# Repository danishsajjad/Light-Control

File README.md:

# Light-Control
 MEL 1 project.

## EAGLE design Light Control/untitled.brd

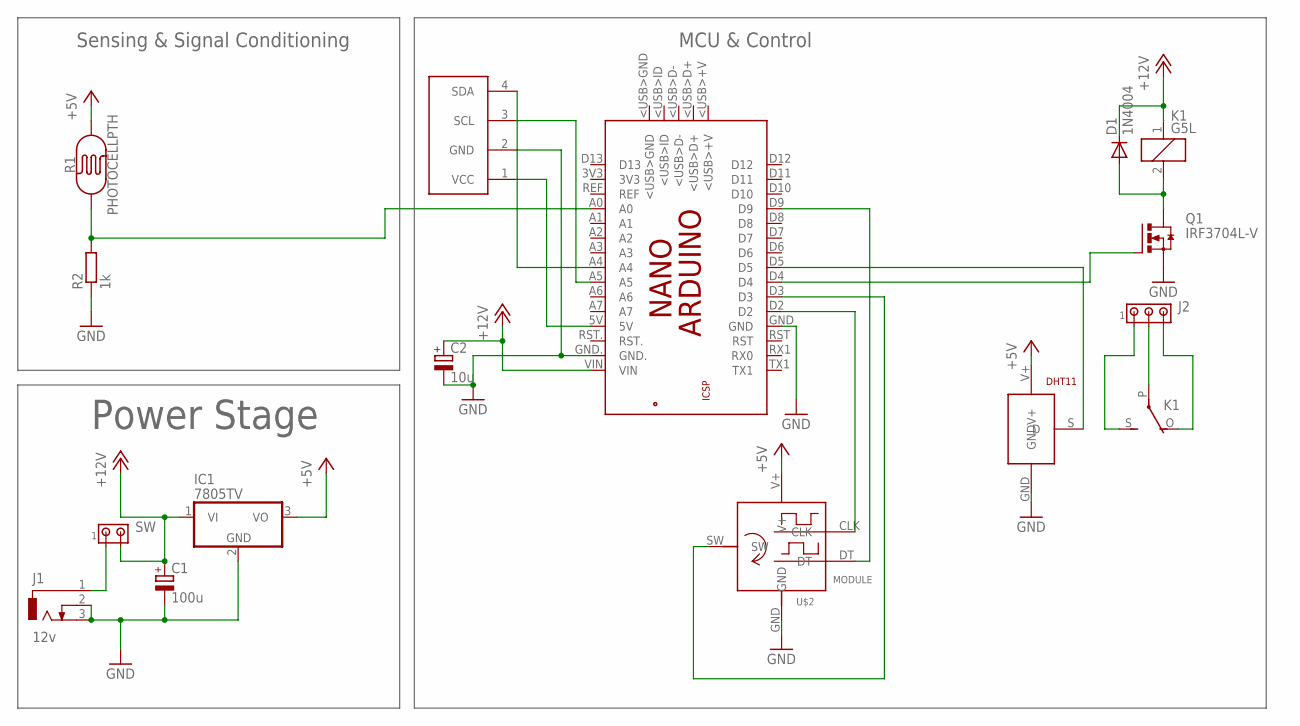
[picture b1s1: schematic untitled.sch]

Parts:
C1: 100u; E3,5-8
C2: 10u; E3,5-8
D1: 1N4004; DO41-10
DHT11: DHT11
IC1: 7805TV; TO220V
J1: 12v; DCJ0303
J2: MTA03-156; 1X3MTA
K1: G5L; G5LE
PCB1: ARDUINO_NANO
Q1: IRF3704L-V; TO262-V
R1: PHOTOCELLPTH; PHOTOCELL
R2: 1k; 0207/7
SW: MTA02-156; 1X2MTA
U$1: I2C_OLED; I2C_OLED_PACKAGE
U$2: MODULE; MODULE/SHEILD

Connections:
+5V: DHT11.V+, IC1.3 (VO), R1.2, U$2.V+
+12V: C1.+, C2.+, D1.C, IC1.1 (VI), K1.1, PCB1.VIN, SW.2
GND: C1.-, C2.-, DHT11.GND, IC1.2 (GND), J1.2, J1.3, PCB1.GND, PCB1.GND., Q1.3 (S), R2.1, U$1.2 (GND), U$2.GND
unnamed: PCB1.A0, R1.1, R2.2
unnamed: PCB1.A4, U$1.4 (SDA)
unnamed: PCB1.A5, U$1.3 (SCL)
unnamed: J1.1, SW.1
unnamed: PCB1.D2, U$2.CLK
unnamed: J2.1, K1.S
unnamed: PCB1.D9, U$2.DT
unnamed: J2.2, K1.P
unnamed: J2.3, K1.O
unnamed: PCB1.D3, U$2.SW
unnamed: DHT11.S (D), PCB1.D5
unnamed: PCB1.5V, U$1.1 (VCC)
unnamed: D1.A, K1.2, Q1.2 (D)
unnamed: PCB1.D4, Q1.1 (G)

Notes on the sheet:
Power Stage
Sensing & Signal Conditioning
MCU & Control

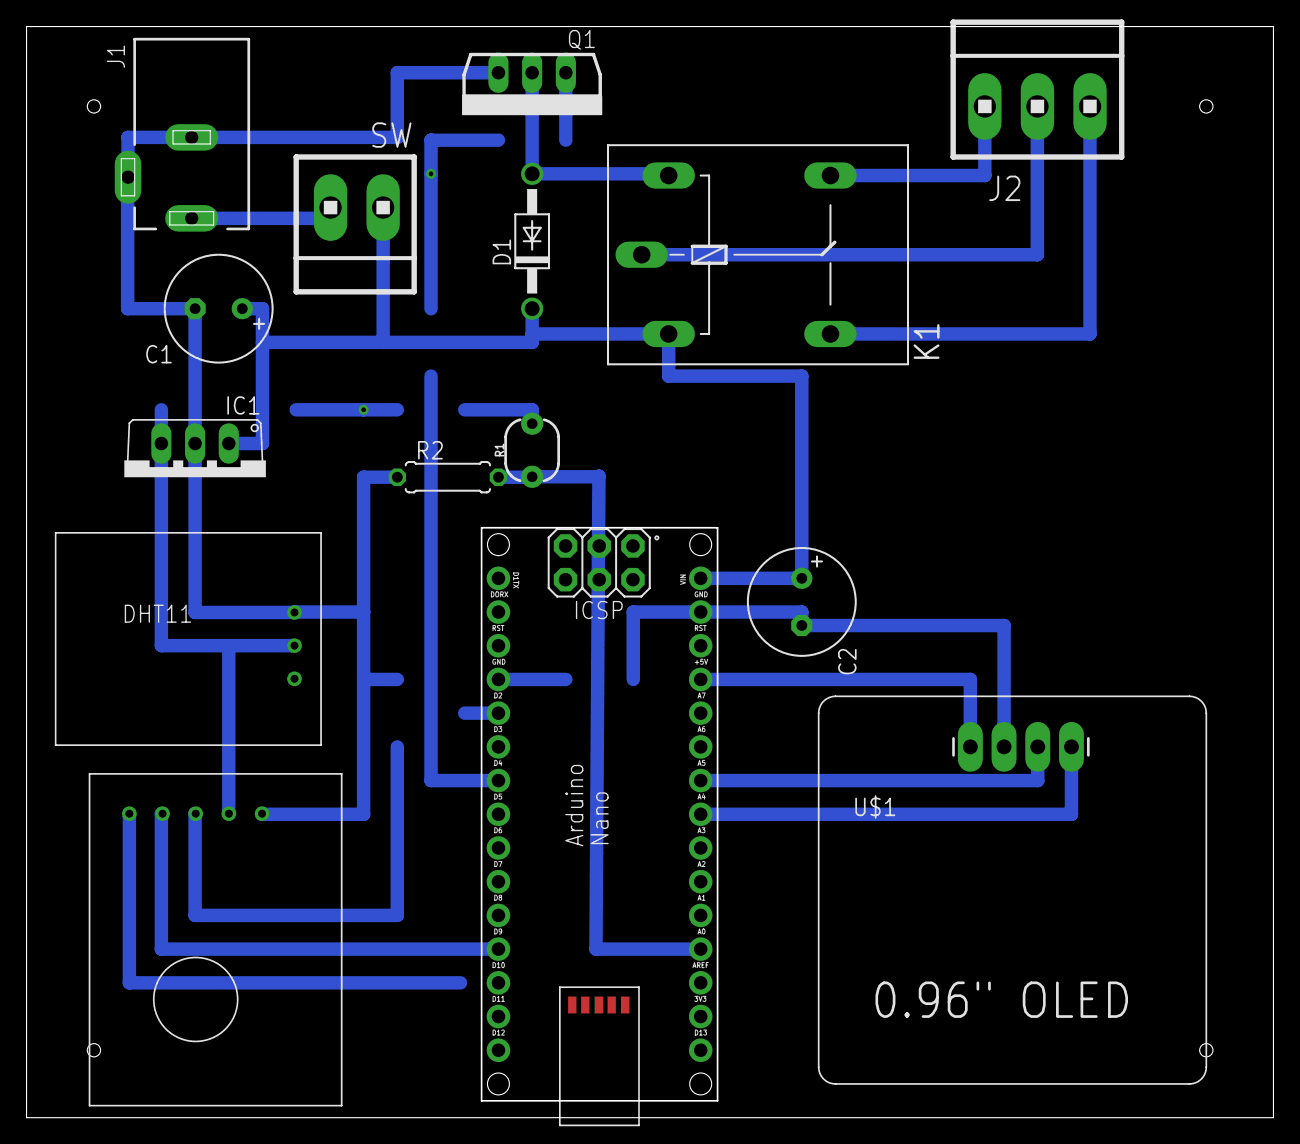
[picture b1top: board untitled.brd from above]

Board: 2 copper layers, 93.8 x 82.1 mm, 15 parts (0 on the bottom side), 17 nets.

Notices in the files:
parts and their libraries:
SparkFun-Sensors: Licensing: Creative Commons ShareAlike 4.0 International - https://creativecommons.org/licenses/by-sa/4.0
